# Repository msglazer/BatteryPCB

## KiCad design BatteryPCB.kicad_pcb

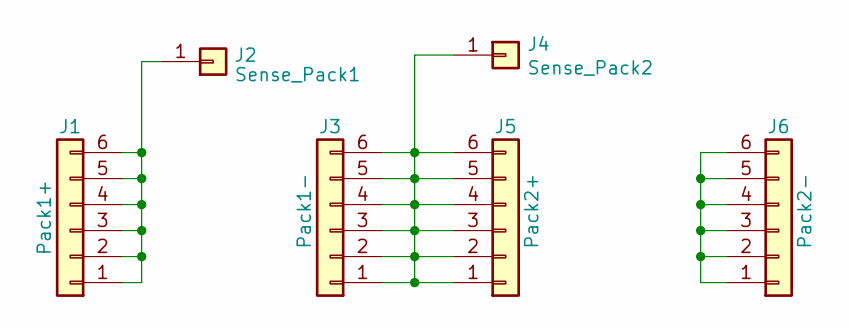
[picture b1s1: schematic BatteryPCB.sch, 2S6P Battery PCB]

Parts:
J1: Pack1+; 6P_ExternalCellTerminal
J2: Sense_Pack1; PinHeader_1x01_P2.54mm_Vertical
J3: Pack1-; 6P_InternalCellTerminal
J4: Sense_Pack2; PinHeader_1x01_P2.54mm_Vertical
J5: Pack2+; 6P_InternalCellTerminal
J6: Pack2-; 6P_ExternalCellTerminal

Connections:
unnamed: J1.1, J1.2, J1.3, J1.4, J1.5, J1.6, J2.1
unnamed: J3.1, J3.2, J3.3, J3.4, J3.5, J3.6, J4.1, J5.1, J5.2, J5.3, J5.4, J5.5, J5.6
unnamed: J6.1, J6.2, J6.3, J6.4, J6.5, J6.6

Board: 2 copper layers, 6 parts (0 on the bottom side), 3 nets, no tracks yet.

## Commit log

2019-06-08 18650 Battery PCB started
2019-06-10 PCB is pretty much done, still need to tweak outline and silkscreen
2019-06-10 finished the copper pours, worked on silkscreen
